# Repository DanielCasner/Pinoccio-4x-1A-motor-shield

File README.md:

Pinoccio 4x 1A motor shield
===========================

Schematic and board layout for a motor driver shield for the Pinoccio <http://pinocc.io>
that will handle up to for channels at up to 1A each with motor voltages between 2.5V
and 15V.

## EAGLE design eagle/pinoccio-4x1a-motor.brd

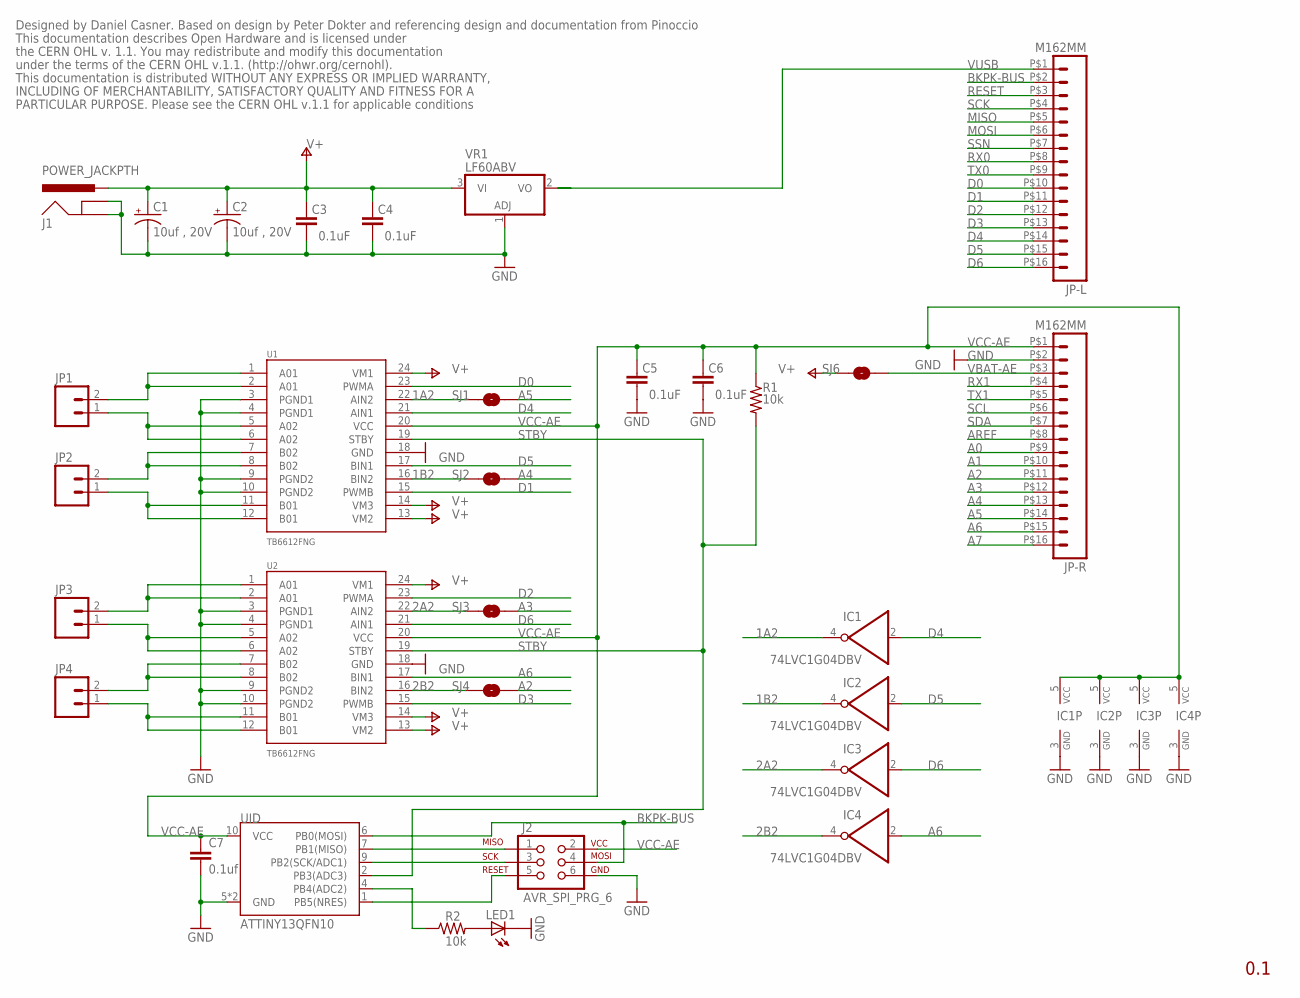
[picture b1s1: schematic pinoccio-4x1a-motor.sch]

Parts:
C1, C2: 10uf , 20V; EIA3528
C3, C4, C5, C6: 0.1uF; 0402-CAP
C7: 0.1uf; 0402-CAP
IC1, IC2, IC3, IC4: 74LVC1G04DBV; SOT23-5
J1: POWER_JACKPTH; POWER_JACK_PTH
J2: AVR_SPI_PRG_6; 2X3-PAD
JP1, JP2, JP3, JP4: M02LOCK_LONGPADS; 1X02_LOCK_LONGPADS
JP-L: M162MM; 1X16_2MM
JP-R: M162MM; 1X16_2MM
LED1: LED0603; LED-0603
R1, R2: 10k; R0402
SJ1, SJ2, SJ3, SJ4, SJ6: SOLDERJUMPERNC2; SJ_2S-NOTRACE
U1, U2: TB6612FNG; SSOP24
UID: ATTINY13QFN10; QFN-10
VR1: LF60ABV; TO220H

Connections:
1A2: IC1.4 (O), SJ1.1, U1.22 (AIN2)
1B2: IC2.4 (O), SJ2.1, U1.16 (BIN2)
2A2: IC3.4 (O), SJ3.1, U2.22 (AIN2)
2B2: IC4.4 (O), SJ4.1, U2.16 (BIN2)
A0: JP-R.P$9 (9)
A1: JP-R.P$10 (10)
A2: JP-R.P$11 (11), SJ4.2
A3: JP-R.P$12 (12), SJ3.2
A4: JP-R.P$13 (13), SJ2.2
A5: JP-R.P$14 (14), SJ1.2
A6: IC4.2 (I), JP-R.P$15 (15), U2.17 (BIN1)
A7: JP-R.P$16 (16)
AREF: JP-R.P$8 (8)
BKPK-BUS: J2.4, JP-L.P$2 (2), UID.6 (PB0(MOSI))
D0: JP-L.P$10 (10), U1.23 (PWMA)
D1: JP-L.P$11 (11), U1.15 (PWMB)
D2: JP-L.P$12 (12), U2.23 (PWMA)
D3: JP-L.P$13 (13), U2.15 (PWMB)
D4: IC1.2 (I), JP-L.P$14 (14), U1.21 (AIN1)
D5: IC2.2 (I), JP-L.P$15 (15), U1.17 (BIN1)
D6: IC3.2 (I), JP-L.P$16 (16), U2.21 (AIN1)
GND: C1.C (-), C2.C (-), C3.1, C4.1, C5.1, C6.1, C7.2, IC1.3 (GND), IC2.3 (GND), IC3.3 (GND), IC4.3 (GND), J1.GND, J1.GNDBREAK, J2.6, JP-R.P$2 (2), LED1.C, U1.3 (PGND1), U1.4 (PGND1), U1.9 (PGND2), U1.10 (PGND2), U1.18 (GND), U2.3 (PGND1), U2.4 (PGND1), U2.9 (PGND2), U2.10 (PGND2), U2.18 (GND), UID.5 (GND), UID.EP (GND), VR1.1 (ADJ)
M1+: JP1.2, U1.1 (A01), U1.2 (A01)
M1-: JP1.1, U1.5 (A02), U1.6 (A02)
M2+: JP2.2, U1.7 (B02), U1.8 (B02)
M2-: JP2.1, U1.11 (B01), U1.12 (B01)
M3+: JP3.2, U2.1 (A01), U2.2 (A01)
M3-: JP3.1, U2.5 (A02), U2.6 (A02)
M4+: JP4.2, U2.7 (B02), U2.8 (B02)
M4-: JP4.1, U2.11 (B01), U2.12 (B01)
MISO: JP-L.P$5 (5)
MOSI: JP-L.P$6 (6)
unnamed: R2.1, UID.4 (PB4(ADC2))
unnamed: J2.1, UID.7 (PB1(MISO))
unnamed: J2.3, UID.9 (PB2(SCK/ADC1))
unnamed: J2.5, UID.1 (PB5(NRES))
unnamed: LED1.A, R2.2
RESET: JP-L.P$3 (3)
RX0: JP-L.P$8 (8)
RX1: JP-R.P$4 (4)
SCK: JP-L.P$4 (4)
SCL: JP-R.P$6 (6)
SDA: JP-R.P$7 (7)
SSN: JP-L.P$7 (7)
STBY: R1.2, U1.19 (STBY), U2.19 (STBY), UID.2 (PB3(ADC3))
TX0: JP-L.P$9 (9)
TX1: JP-R.P$5 (5)
V+: C1.A (+), C2.A (+), C3.2, C4.2, J1.PWR, SJ6.1, U1.13 (VM2), U1.14 (VM3), U1.24 (VM1), U2.13 (VM2), U2.14 (VM3), U2.24 (VM1), VR1.3 (VI)
VBAT-AE: JP-R.P$3 (3), SJ6.2
VCC-AE: C5.2, C6.2, C7.1, IC1.5 (VCC), IC2.5 (VCC), IC3.5 (VCC), IC4.5 (VCC), J2.2, JP-R.P$1 (1), R1.1, U1.20 (VCC), U2.20 (VCC), UID.10 (VCC)
VUSB: JP-L.P$1 (1), VR1.2 (VO)

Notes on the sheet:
0.1
Designed by Daniel Casner. Based on design by Peter Dokter and referencing design and documentation from Pinoccio
This documentation describes Open Hardware and is licensed under
the CERN OHL v. 1.1. You may redistribute and modify this documentation
under the terms of the CERN OHL v.1.1. (http://ohwr.org/cernohl).
This documentation is distributed WITHOUT ANY EXPRESS OR IMPLIED WARRANTY,
INCLUDING OF MERCHANTABILITY, SATISFACTORY QUALITY AND FITNESS FOR A
PARTICULAR PURPOSE. Please see the CERN OHL v.1.1 for applicable conditions

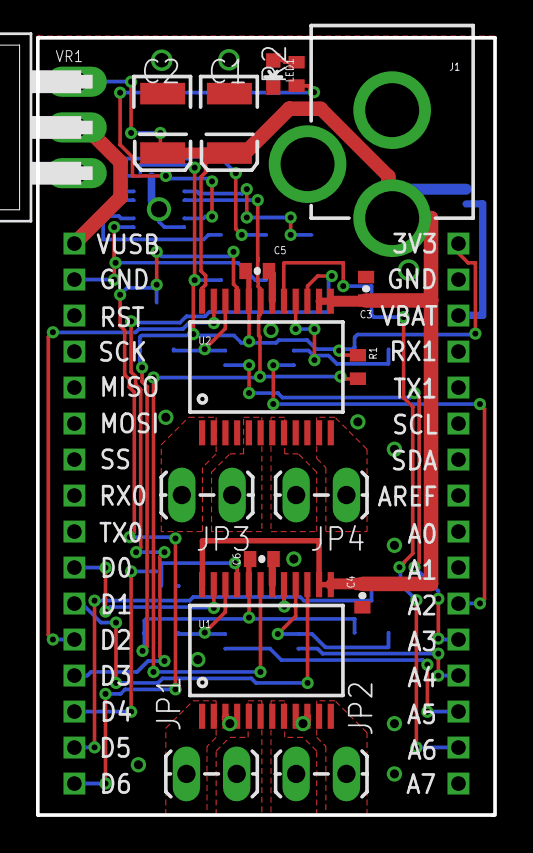
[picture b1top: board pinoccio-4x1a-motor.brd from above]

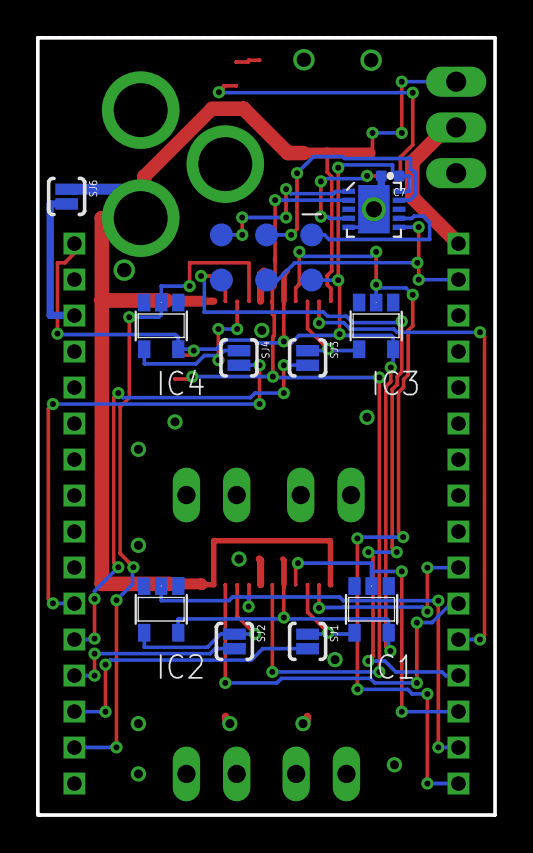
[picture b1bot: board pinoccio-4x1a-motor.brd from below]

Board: 2 copper layers, 25.4 x 43.2 mm, 31 parts (12 on the bottom side), 36 nets.

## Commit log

2013-02-25 First commit of new shield.
    Main components added, no signals.
2013-03-16 Finish first draft of schematic
    Initial placement.
    Add design rules file from OSHPark.com
    Export PDFs of schematic and board.
2013-05-05 Change layout onto an Arduino shield compatible board.
2013-05-05 High current traces routed.
2013-06-09 Working on manual routing.
2013-06-09 A tiny bit more work. Putting everything on hold until the new backpack interface is documented.
2013-06-14 Finish routing with auto-router. Export PDFs of schematic and board.
2013-06-14 Add .pro files to ignore
2013-06-14 Add Atiny13 backpack ID chip. Connect LED and backpack standby to unused GPIO pins on the ATiny13.
2013-06-17 Move components around to accommodate required standard position of the backpack programming pads.
2013-06-17 Tru ripping up all the autorouted signals before rerouting.
2013-06-17 Successful reroute with rearranged components. Note there is now a via under the ground pad for the ATtiny13. This should actually make it easier to hand solder.

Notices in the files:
eagle/pinoccio-4x1a-motor.brd:
Licensed under CERN OHL v.1.1
parts and their libraries:
SparkFun-Connectors: Licensing: CC v3.0 Share-Alike You are welcome to use this library for commercial purposes.
